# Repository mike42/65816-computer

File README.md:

# 65816 computer 

This is a prototype 65C816-based computer. It features a 1.8432 MHz processor, 1 megabyte of static RAM, a 65C22 I/O port, and an NXP SC16C752 dual UART.

The ROM contains a simple test program.

## Blog series

This is a learning project, and I am blogging about it as I progress.

- [A first look at the 65C816 processor](https://mike42.me/blog/2022-01-a-first-look-at-the-65c816-processor)
- [65C816 computer - initial prototype](https://mike42.me/blog/2022-02-65c816-computer-initial-prototype)
- [Interfacing an NXP UART to an 8-bit computer](https://mike42.me/blog/2022-02-interfacing-an-nxp-uart-to-an-8-bit-computer)
- [Let’s implement preemptive multitasking](https://mike42.me/blog/2022-03-lets-implement-preemptive-multitasking)
- [Building an emulator for my 65C816 computer](https://mike42.me/blog/2022-04-building-an-emulator-for-my-65c816-computer)
- [65C816 computer - second prototype](https://mike42.me/blog/2022-05-65c816-computer-second-prototype)
- [Building a 65C816 test board](https://mike42.me/blog/2022-06-building-a-65c816-test-board)
- [Let’s implement power-on self test (POST)](https://mike42.me/blog/2022-06-lets-implement-power-on-self-test-post)
- [Let’s make a bootloader – Part 1](https://mike42.me/blog/2022-09-lets-make-a-bootloader-part-1)
- [Let’s make a bootloader – Part 2](https://mike42.me/blog/2022-09-lets-make-a-bootloader-part-2)
- [Converting my 65C816 computer project to 3.3 V](https://mike42.me/blog/2023-01-converting-my-65c816-computer-project-to-3-3-v)

## Licenses & acknowledgement

With the exception of the files noted below, this work is © 2022-2023 Michael Billington, and is licensed under a [Creative Commons Attribution 4.0 International License](http://creativecommons.org/licenses/by/4.0/).

### 65816 emulator

The files in the `emulator/` directory are derived from Francesco Rigoni's work, primarily [lib65816](https://github.com/FrancescoRigoni/Lib65816). The emulator application is licensed under the GNU General Public License, version 3. Please see the README and LICENSE file in that directory for details.

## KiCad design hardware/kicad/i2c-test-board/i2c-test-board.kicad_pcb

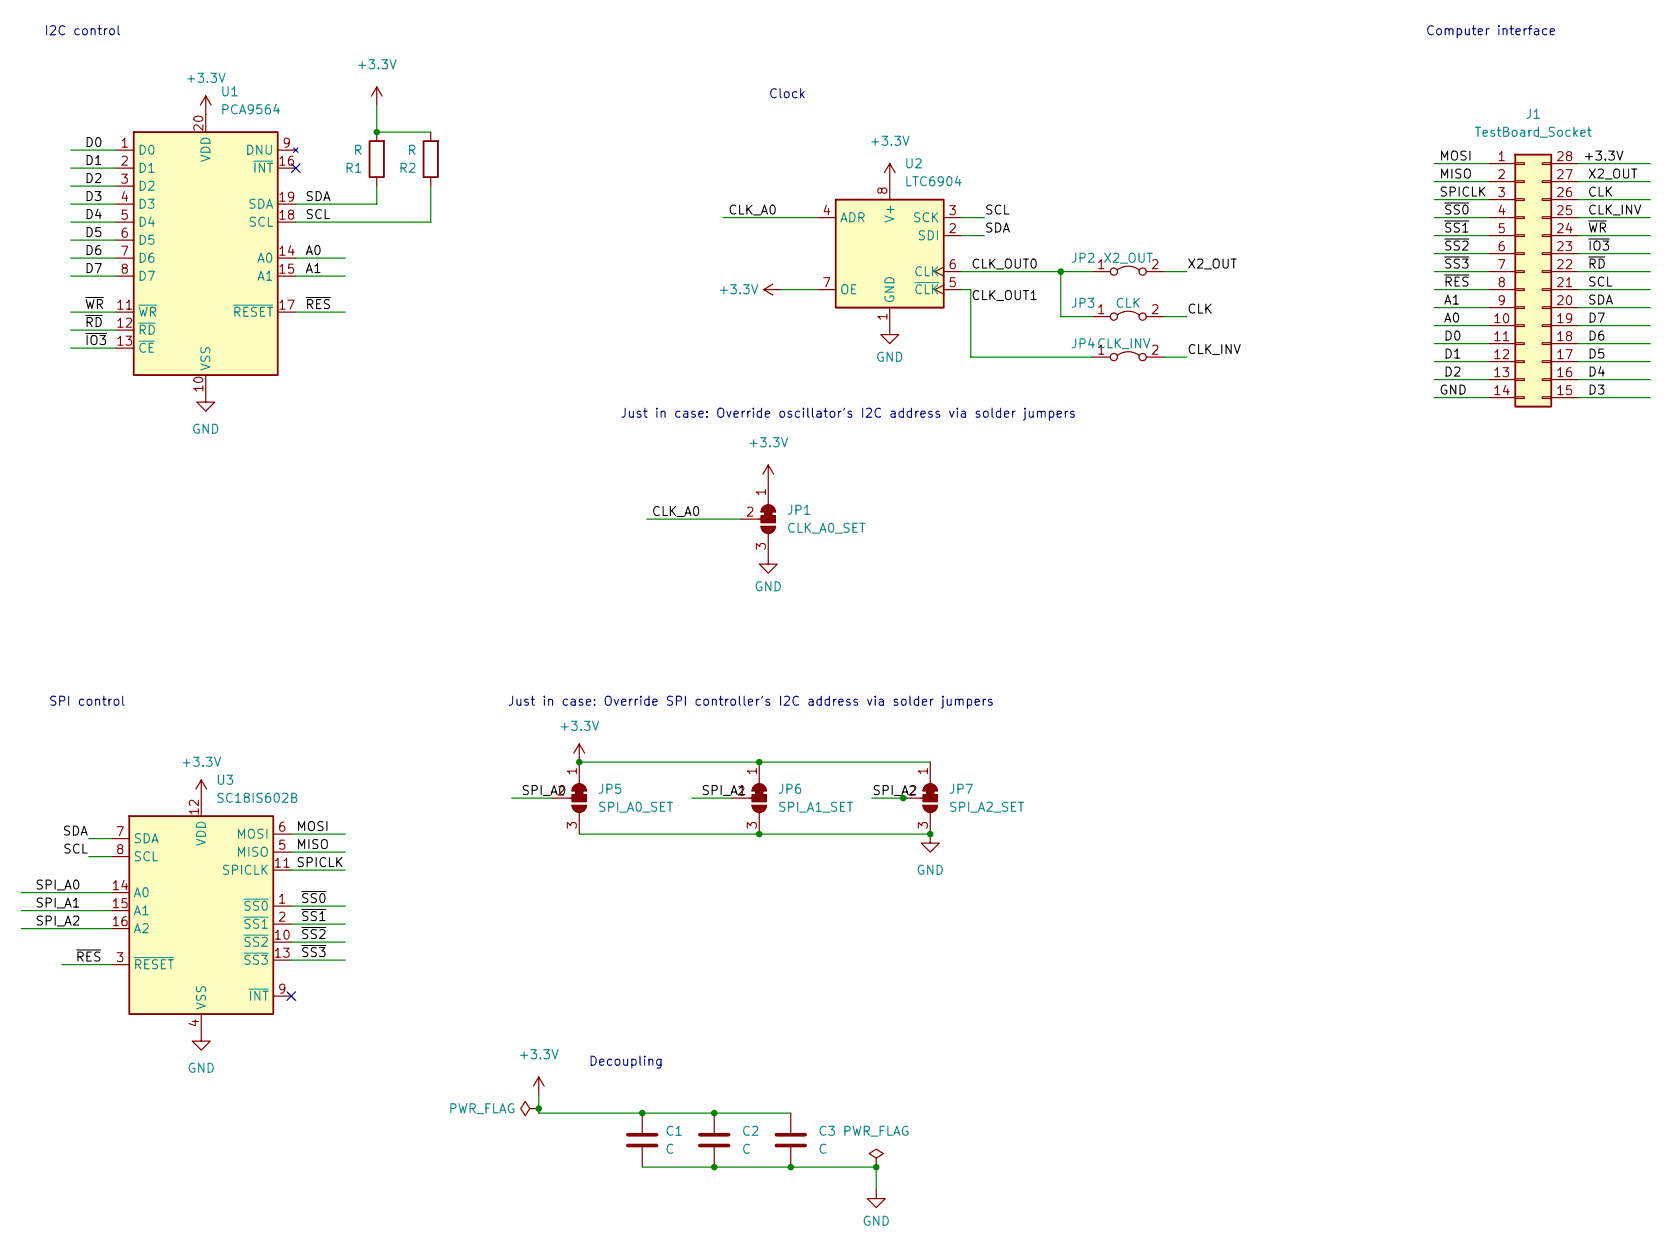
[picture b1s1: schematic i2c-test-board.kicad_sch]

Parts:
C1, C2, C3: C; C_0603_1608Metric_Pad1.08x0.95mm_HandSolder
J1: TestBoard_Socket; DIP-28_W15.24mm_Socket
JP1: CLK_A0_SET; SolderJumper-3_P1.3mm_Bridged12_RoundedPad1.0x1.5mm
JP2: X2_OUT; SolderJumper-2_P1.3mm_Bridged_RoundedPad1.0x1.5mm
JP3: CLK; SolderJumper-2_P1.3mm_Bridged_RoundedPad1.0x1.5mm
JP4: CLK_INV; SolderJumper-2_P1.3mm_Bridged_RoundedPad1.0x1.5mm
JP5: SPI_A0_SET; SolderJumper-3_P1.3mm_Bridged12_RoundedPad1.0x1.5mm
JP6: SPI_A1_SET; SolderJumper-3_P1.3mm_Bridged12_RoundedPad1.0x1.5mm
JP7: SPI_A2_SET; SolderJumper-3_P1.3mm_Bridged12_RoundedPad1.0x1.5mm
R1, R2: R; R_0603_1608Metric_Pad0.98x0.95mm_HandSolder
U1: PCA9564; TSSOP-20_4.4x6.5mm_P0.65mm
U2: LTC6904; MSOP-8_3x3mm_P0.65mm
U3: SC18IS602B; TSSOP-16_4.4x5mm_P0.65mm

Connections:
+3.3V: C1.1, C2.1, C3.1, J1.28, JP1.1 (A), JP5.1 (A), JP6.1 (A), JP7.1 (A), R1.2, R2.2, U1.20 (VDD), U2.7 (OE), U2.8 (V+), U3.12 (VDD)
/A0: J1.10, U1.14 (A0)
/A1: J1.9, U1.15 (A1)
/CLK: J1.26, JP3.2 (B)
/CLK_A0: JP1.2 (C), U2.4 (ADR)
/CLK_INV: J1.25, JP4.2 (B)
/CLK_OUT0: JP2.1 (A), JP3.1 (A), U2.6 (CLK)
/CLK_OUT1: JP4.1 (A), U2.5 (~CLK)
/D0: J1.11, U1.1 (D0)
/D1: J1.12, U1.2 (D1)
/D2: J1.13, U1.3 (D2)
/D3: J1.15, U1.4 (D3)
/D4: J1.16, U1.5 (D4)
/D5: J1.17, U1.6 (D5)
/D6: J1.18, U1.7 (D6)
/D7: J1.19, U1.8 (D7)
/MISO: J1.2, U3.5 (MISO)
/MOSI: J1.1, U3.6 (MOSI)
/SCL: J1.21, R2.1, U1.18 (SCL), U2.3 (SCK), U3.8 (SCL)
/SDA: J1.20, R1.1, U1.19 (SDA), U2.2 (SDI), U3.7 (SDA)
/SPICLK: J1.3, U3.11 (SPICLK)
/SPI_A0: JP5.2 (C), U3.14 (A0)
/SPI_A1: JP6.2 (C), U3.15 (A1)
/SPI_A2: JP7.2 (C), U3.16 (A2)
/X2_OUT: J1.27, JP2.2 (B)
/~IO3: J1.23, U1.13 (~CE)
/~RD: J1.22, U1.12 (~RD)
/~RES: J1.8, U1.17 (~RESET), U3.3 (~RESET)
/~SS0: J1.4, U3.1 (~SS0)
/~SS1: J1.5, U3.2 (~SS1)
/~SS2: J1.6, U3.10 (~SS2)
/~SS3: J1.7, U3.13 (~SS3)
/~WR: J1.24, U1.11 (~WR)
GND: C1.2, C2.2, C3.2, J1.14, JP1.3 (B), JP5.3 (B), JP6.3 (B), JP7.3 (B), U1.10 (VSS), U2.1 (GND), U3.4 (VSS)

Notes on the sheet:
I2C control
Just in case: Override oscillator's I2C address via solder jumpers
Computer interface
Clock
Decoupling
SPI control
Just in case: Override SPI controller's I2C address via solder jumpers

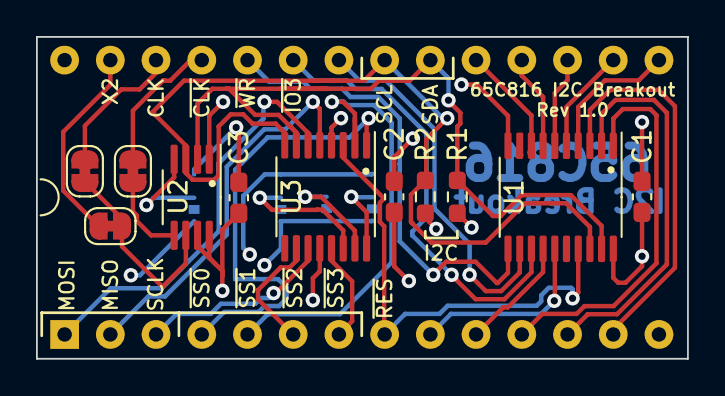
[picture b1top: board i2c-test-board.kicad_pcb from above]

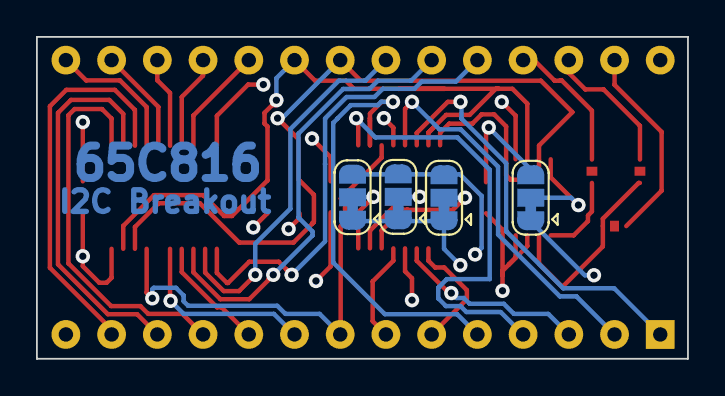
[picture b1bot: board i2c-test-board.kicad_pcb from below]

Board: 4 copper layers, 36.2 x 17.9 mm, 16 parts (4 on the bottom side), 34 nets.

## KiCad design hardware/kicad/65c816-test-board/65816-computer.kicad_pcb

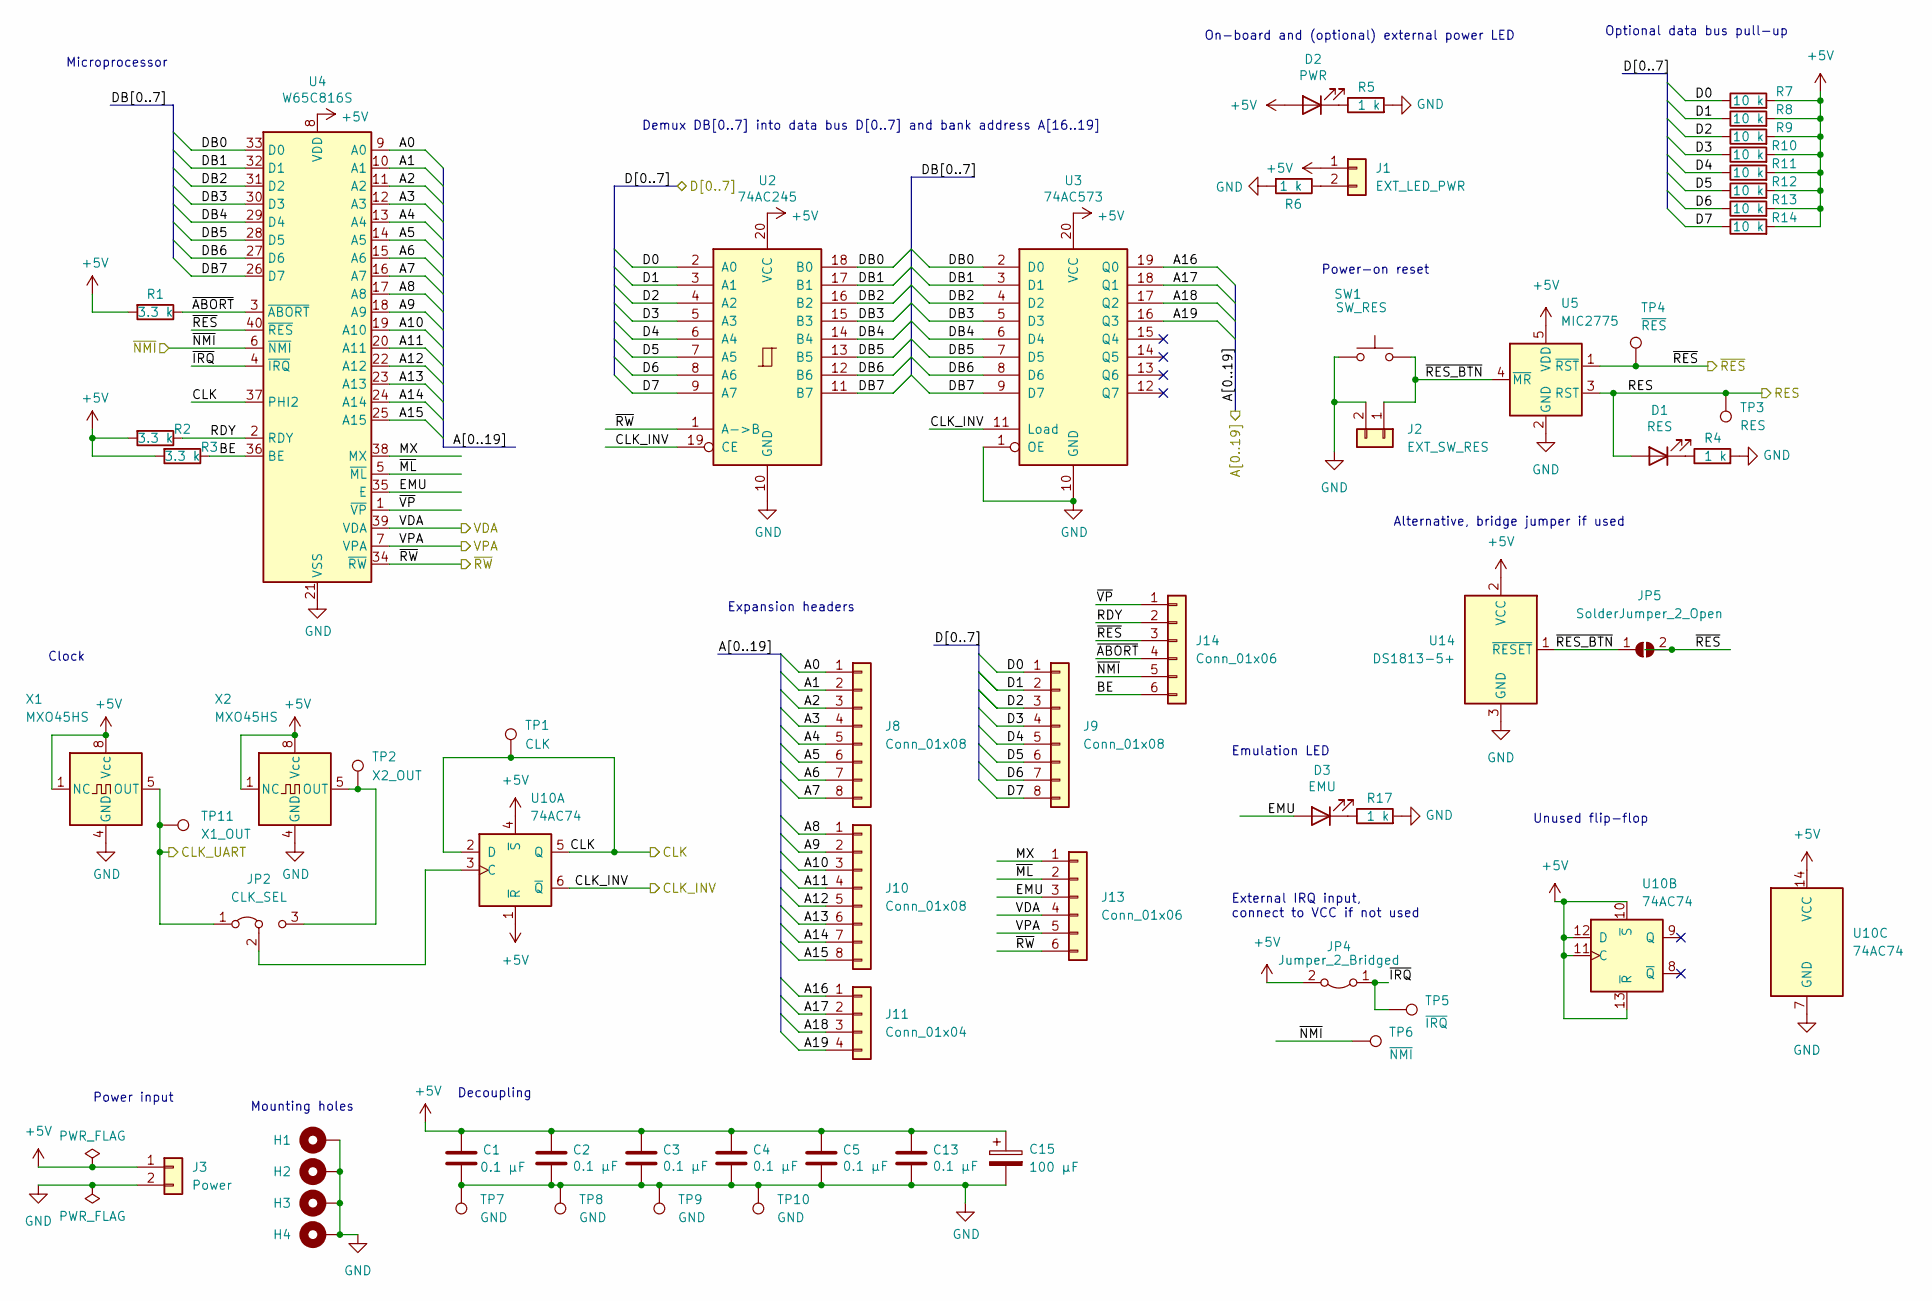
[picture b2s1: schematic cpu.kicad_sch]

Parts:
C1, C2, C3, C4, C5, C13: 0.1 µF; C_0603_1608Metric_Pad1.08x0.95mm_HandSolder
C15: 100 µF; CP_Radial_D6.3mm_P2.50mm
D1: RES; LED_0603_1608Metric_Pad1.05x0.95mm_HandSolder
D2: PWR; LED_0603_1608Metric_Pad1.05x0.95mm_HandSolder
D3: EMU; LED_0603_1608Metric_Pad1.05x0.95mm_HandSolder
H1, H2, H3, H4: MountingHole_Pad; MountingHole_3.2mm_M3_Pad_Via
J1: EXT_LED_PWR; PinHeader_1x02_P2.54mm_Vertical
J2: EXT_SW_RES; PinHeader_1x02_P2.54mm_Vertical
J3: Power; JST_XH_B2B-XH-A_1x02_P2.50mm_Vertical
J8, J9, J10: Conn_01x08; PinHeader_1x08_P2.54mm_Vertical
J11: Conn_01x04; PinHeader_1x04_P2.54mm_Vertical
J13, J14: Conn_01x06; PinHeader_1x06_P2.54mm_Vertical
JP2: CLK_SEL; PinHeader_1x03_P2.54mm_Vertical
JP4: Jumper_2_Bridged; PinHeader_1x02_P2.54mm_Vertical
JP5: SolderJumper_2_Open; SolderJumper-2_P1.3mm_Open_RoundedPad1.0x1.5mm
R1, R2, R3: 3.3 k; R_0603_1608Metric_Pad0.98x0.95mm_HandSolder
R4, R5, R6, R17: 1 k; R_0603_1608Metric_Pad0.98x0.95mm_HandSolder
R7, R8, R9, R10, R11, R12, R13, R14: 10 k; R_0603_1608Metric_Pad0.98x0.95mm_HandSolder
SW1: SW_RES; SW_TH_Tactile_Omron_B3F-10xx
TP1: CLK; TestPoint_Keystone_5005-5009_Compact
TP2: X2_OUT; TestPoint_Keystone_5005-5009_Compact
TP3: RES; TestPoint_Pad_D1.5mm
TP4: ~{RES}; TestPoint_Keystone_5005-5009_Compact
TP5: ~{IRQ}; TestPoint_Keystone_5005-5009_Compact
TP6: ~{NMI}; TestPoint_Keystone_5005-5009_Compact
TP7, TP8, TP9, TP10: GND; TestPoint_Keystone_5005-5009_Compact
TP11: X1_OUT; TestPoint_Keystone_5005-5009_Compact
U2: 74AC245; DIP-20_W7.62mm_Socket
U3: 74AC573; DIP-20_W7.62mm_Socket
U4: W65C816S; DIP-40_W15.24mm_Socket
U5: MIC2775; SOT-23-5_HandSoldering
U10: 74AC74; DIP-14_W7.62mm_Socket
U14: DS1813-5+; TO-92_Inline
X1, X2: MXO45HS; Oscillator_DIP-8

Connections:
+5V: C1.1, C2.1, C3.1, C4.1, C5.1, C13.1, C15.1, D2.2 (A), J1.1, J3.1, JP4.2 (B), R1.2, R2.2, R3.2, R7.2, R8.2, R9.2, R10.2, R11.2, R12.2, R13.2, R14.2, U2.20 (VCC), U3.20 (VCC), U4.8 (VDD), U5.5 (VDD), U10.1 (~R), U10.4 (~S), U10.10 (~S), U10.11 (C), U10.12 (D), U10.13 (~R), U10.14 (VCC), U14.2 (VCC), X1.1 (NC), X1.8 (Vcc), X2.1 (NC), X2.8 (Vcc); also elsewhere on the board
/CPU& Bank Address Latching/A0: J8.1, U4.9 (A0); also elsewhere on the board
/CPU& Bank Address Latching/A1: J8.2, U4.10 (A1); also elsewhere on the board
/CPU& Bank Address Latching/A2: J8.3, U4.11 (A2); also elsewhere on the board
/CPU& Bank Address Latching/A3: J8.4, U4.12 (A3); also elsewhere on the board
/CPU& Bank Address Latching/A4: J8.5, U4.13 (A4); also elsewhere on the board
/CPU& Bank Address Latching/A5: J8.6, U4.14 (A5); also elsewhere on the board
/CPU& Bank Address Latching/A6: J8.7, U4.15 (A6); also elsewhere on the board
/CPU& Bank Address Latching/A7: J8.8, U4.16 (A7); also elsewhere on the board
/CPU& Bank Address Latching/A8: J10.1, U4.17 (A8); also elsewhere on the board
/CPU& Bank Address Latching/A9: J10.2, U4.18 (A9); also elsewhere on the board
/CPU& Bank Address Latching/A10: J10.3, U4.19 (A10); also elsewhere on the board
/CPU& Bank Address Latching/A11: J10.4, U4.20 (A11); also elsewhere on the board
/CPU& Bank Address Latching/A12: J10.5, U4.22 (A12); also elsewhere on the board
/CPU& Bank Address Latching/A13: J10.6, U4.23 (A13); also elsewhere on the board
/CPU& Bank Address Latching/A14: J10.7, U4.24 (A14); also elsewhere on the board
/CPU& Bank Address Latching/A15: J10.8, U4.25 (A15); also elsewhere on the board
/CPU& Bank Address Latching/A16: J11.1, U3.19 (Q0); also elsewhere on the board
/CPU& Bank Address Latching/A17: J11.2, U3.18 (Q1); also elsewhere on the board
/CPU& Bank Address Latching/A18: J11.3, U3.17 (Q2); also elsewhere on the board
/CPU& Bank Address Latching/A19: J11.4, U3.16 (Q3); also elsewhere on the board
/CPU& Bank Address Latching/BE: J14.6, R3.1, U4.36 (BE)
/CPU& Bank Address Latching/CLK: TP1.1, U4.37 (PHI2), U10.2 (D), U10.5 (Q); also elsewhere on the board
/CPU& Bank Address Latching/CLK_INV: U2.19 (CE), U3.11 (Load), U10.6 (~Q)
/CPU& Bank Address Latching/CLK_UART: JP2.1 (A), TP11.1, X1.5 (OUT); also elsewhere on the board
/CPU& Bank Address Latching/D0: J9.1, R7.1, U2.2 (A0); also elsewhere on the board
/CPU& Bank Address Latching/D1: J9.2, R8.1, U2.3 (A1); also elsewhere on the board
/CPU& Bank Address Latching/D2: J9.3, R9.1, U2.4 (A2); also elsewhere on the board
/CPU& Bank Address Latching/D3: J9.4, R10.1, U2.5 (A3); also elsewhere on the board
/CPU& Bank Address Latching/D4: J9.5, R11.1, U2.6 (A4); also elsewhere on the board
/CPU& Bank Address Latching/D5: J9.6, R12.1, U2.7 (A5); also elsewhere on the board
/CPU& Bank Address Latching/D6: J9.7, R13.1, U2.8 (A6); also elsewhere on the board
/CPU& Bank Address Latching/D7: J9.8, R14.1, U2.9 (A7); also elsewhere on the board
/CPU& Bank Address Latching/DB0: U2.18 (B0), U3.2 (D0), U4.33 (D0)
/CPU& Bank Address Latching/DB1: U2.17 (B1), U3.3 (D1), U4.32 (D1)
/CPU& Bank Address Latching/DB2: U2.16 (B2), U3.4 (D2), U4.31 (D2)
/CPU& Bank Address Latching/DB3: U2.15 (B3), U3.5 (D3), U4.30 (D3)
/CPU& Bank Address Latching/DB4: U2.14 (B4), U3.6 (D4), U4.29 (D4)
/CPU& Bank Address Latching/DB5: U2.13 (B5), U3.7 (D5), U4.28 (D5)
/CPU& Bank Address Latching/DB6: U2.12 (B6), U3.8 (D6), U4.27 (D6)
/CPU& Bank Address Latching/DB7: U2.11 (B7), U3.9 (D7), U4.26 (D7)
/CPU& Bank Address Latching/EMU: D3.2 (A), J13.3, U4.35 (E)
/CPU& Bank Address Latching/MX: J13.1, U4.38 (MX)
/CPU& Bank Address Latching/RDY: J14.2, R2.1, U4.2 (RDY)
/CPU& Bank Address Latching/RES: D1.2 (A), TP3.1, U5.3 (RST); also elsewhere on the board
/CPU& Bank Address Latching/VDA: J13.4, U4.39 (VDA); also elsewhere on the board
/CPU& Bank Address Latching/VPA: J13.5, U4.7 (VPA); also elsewhere on the board
/CPU& Bank Address Latching/~ABORT: J14.4, R1.1, U4.3 (~ABORT)
/CPU& Bank Address Latching/~IRQ: JP4.1 (A), TP5.1, U4.4 (~IRQ)
/CPU& Bank Address Latching/~ML: J13.2, U4.5 (~ML)
/CPU& Bank Address Latching/~NMI: J14.5, TP6.1, U4.6 (~NMI); also elsewhere on the board
/CPU& Bank Address Latching/~RES_BTN: J2.1, JP5.1 (A), SW1.2, U5.4 (~MR), U14.1 (~RESET)
/CPU& Bank Address Latching/~RES: J14.3, JP5.2 (B), TP4.1, U4.40 (~RES), U5.1 (~RST); also elsewhere on the board
/CPU& Bank Address Latching/~RW: J13.6, U2.1 (A->B), U4.34 (~RW); also elsewhere on the board
/CPU& Bank Address Latching/~VP: J14.1, U4.1 (~VP)
GND: C1.2, C2.2, C3.2, C4.2, C5.2, C13.2, C15.2, H1.1, H2.1, H3.1, H4.1, J2.2, J3.2, R4.2, R5.2, R6.2, R17.2, SW1.1, TP7.1, TP8.1, TP9.1, TP10.1, U2.10 (GND), U3.1 (OE), U3.10 (GND), U4.21 (VSS), U5.2 (GND), U10.7 (GND), U14.3 (GND), X1.4 (GND), X2.4 (GND); also elsewhere on the board
unnamed: D1.1 (K), R4.1
unnamed: D2.1 (K), R5.1
unnamed: D3.1 (K), R17.1
unnamed: J1.2, R6.1
unnamed: JP2.2 (C), U10.3 (C)
unnamed 127: JP2.3 (B), TP2.1, X2.5 (OUT); also elsewhere on the board

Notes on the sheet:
Power input
Unused flip-flop
Expansion headers
On-board and (optional) external power LED
Microprocessor
Clock
Alternative, bridge jumper if used
Emulation LED
Demux DB[0..7] into data bus D[0..7] and bank address A[16..19]
Decoupling
Mounting holes
External IRQ input, connect to VCC if not used
Power-on reset
Optional data bus pull-up

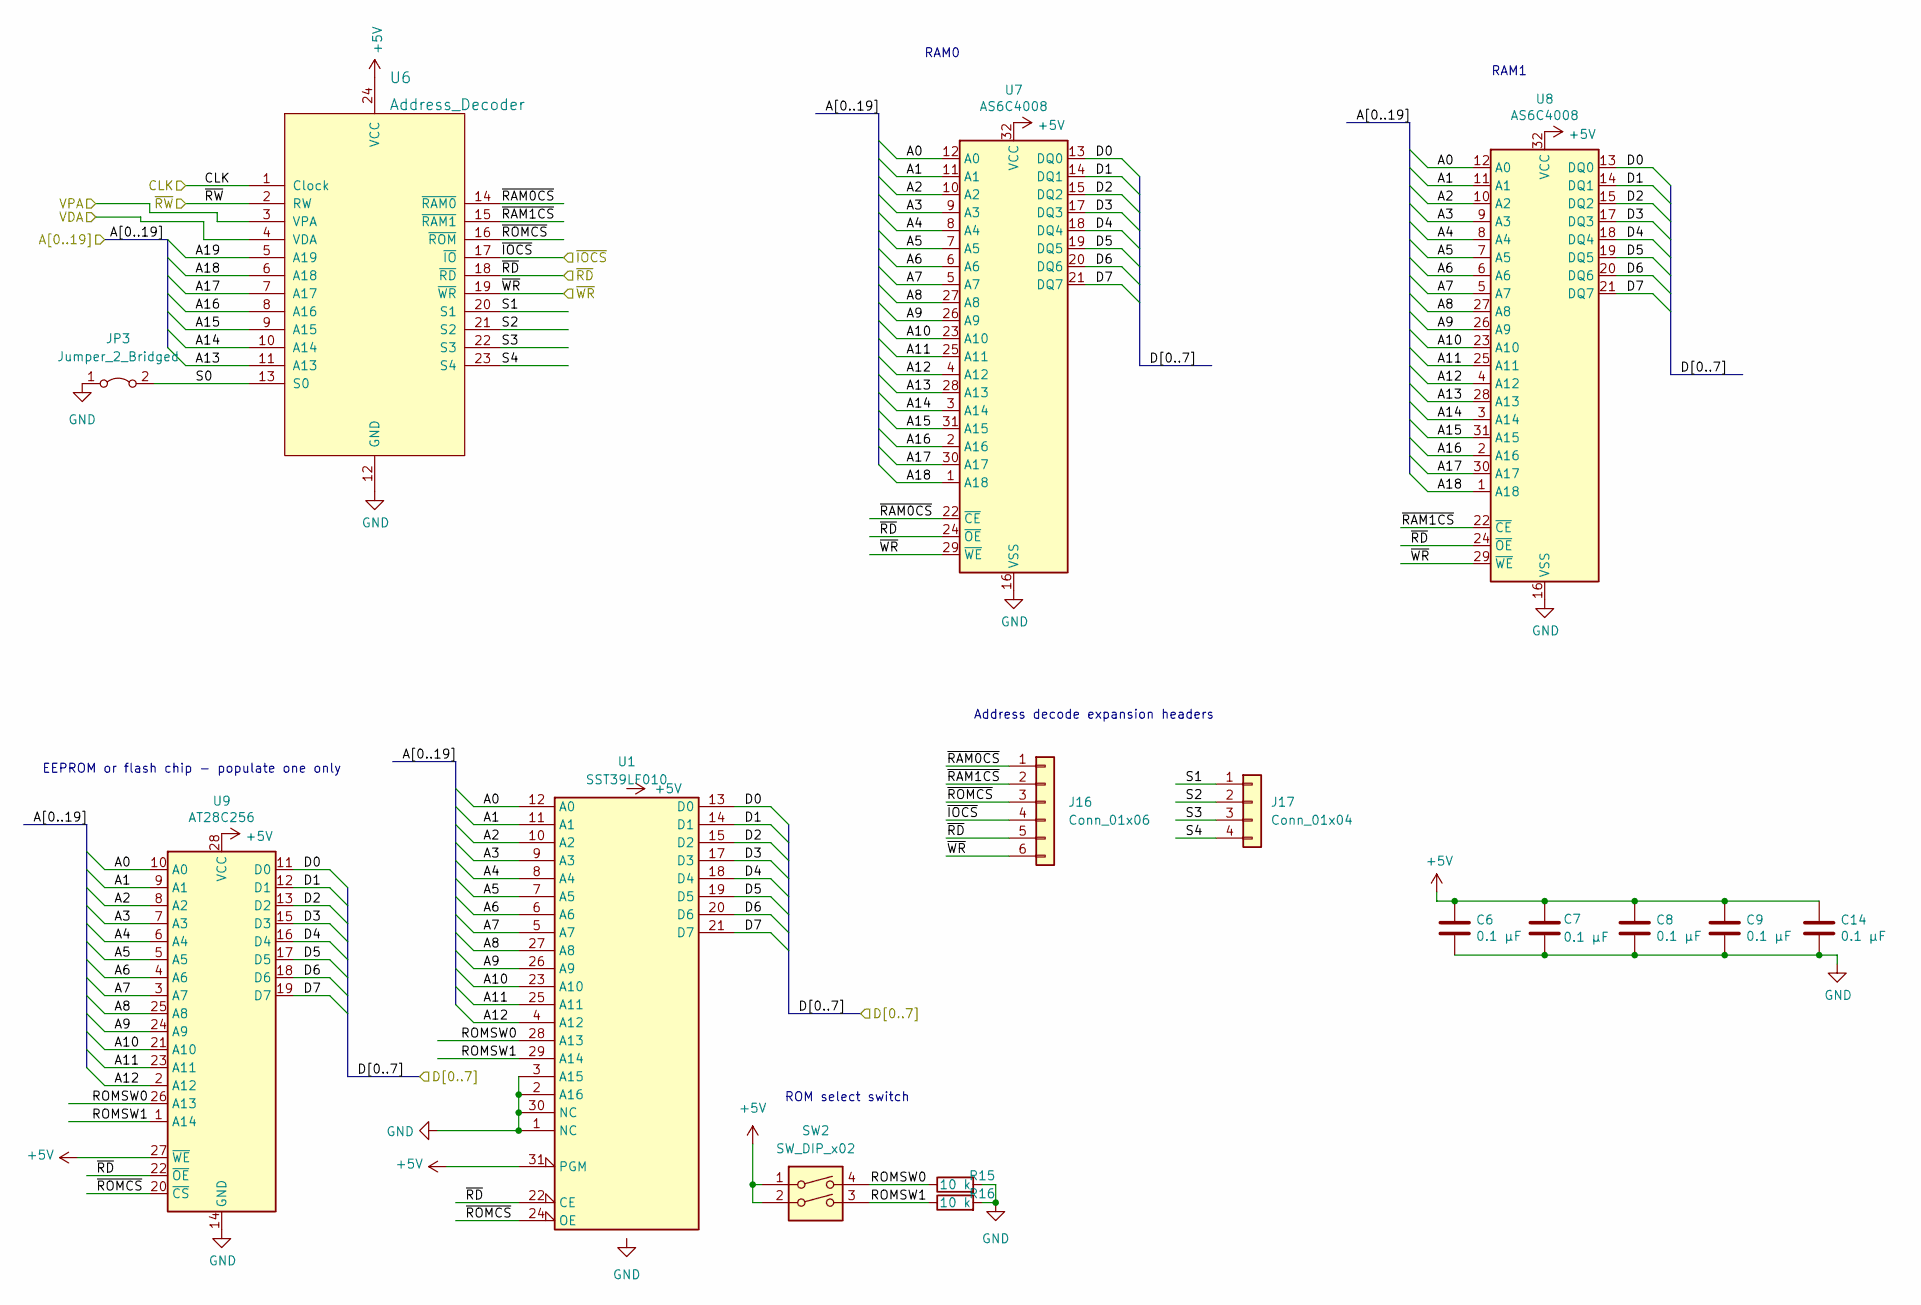
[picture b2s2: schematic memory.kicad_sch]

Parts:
C6, C7, C8, C9, C14: 0.1 µF; C_0603_1608Metric_Pad1.08x0.95mm_HandSolder
J16: Conn_01x06; PinHeader_1x06_P2.54mm_Vertical
J17: Conn_01x04; PinHeader_1x04_P2.54mm_Vertical
JP3: Jumper_2_Bridged; PinHeader_1x02_P2.54mm_Vertical
R15, R16: 10 k; R_0603_1608Metric_Pad0.98x0.95mm_HandSolder
SW2: SW_DIP_x02; SW_DIP_SPSTx02_Slide_6.7x6.64mm_W8.61mm_P2.54mm_LowProfile
U1: SST39LF010; PLCC-32_11.4x14.0mm_P1.27mm
U6: Address_Decoder; DIP-24_W7.62mm_Socket
U7, U8: AS6C4008; DIP-32_W15.24mm_Socket
U9: AT28C256; DIP-28_W15.24mm_Socket

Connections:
+5V: C6.1, C7.1, C8.1, C9.1, C14.1, SW2.1, SW2.2, U1.31 (PGM), U1.32 (VCC), U6.24 (VCC), U7.32 (VCC), U8.32 (VCC), U9.27 (~WE), U9.28 (VCC); also elsewhere on the board
/CPU& Bank Address Latching/A0: U1.12 (A0), U7.12 (A0), U8.12 (A0), U9.10 (A0); also elsewhere on the board
/CPU& Bank Address Latching/A1: U1.11 (A1), U7.11 (A1), U8.11 (A1), U9.9 (A1); also elsewhere on the board
/CPU& Bank Address Latching/A2: U1.10 (A2), U7.10 (A2), U8.10 (A2), U9.8 (A2); also elsewhere on the board
/CPU& Bank Address Latching/A3: U1.9 (A3), U7.9 (A3), U8.9 (A3), U9.7 (A3); also elsewhere on the board
/CPU& Bank Address Latching/A4: U1.8 (A4), U7.8 (A4), U8.8 (A4), U9.6 (A4); also elsewhere on the board
/CPU& Bank Address Latching/A5: U1.7 (A5), U7.7 (A5), U8.7 (A5), U9.5 (A5); also elsewhere on the board
/CPU& Bank Address Latching/A6: U1.6 (A6), U7.6 (A6), U8.6 (A6), U9.4 (A6); also elsewhere on the board
/CPU& Bank Address Latching/A7: U1.5 (A7), U7.5 (A7), U8.5 (A7), U9.3 (A7); also elsewhere on the board
/CPU& Bank Address Latching/A8: U1.27 (A8), U7.27 (A8), U8.27 (A8), U9.25 (A8); also elsewhere on the board
/CPU& Bank Address Latching/A9: U1.26 (A9), U7.26 (A9), U8.26 (A9), U9.24 (A9); also elsewhere on the board
/CPU& Bank Address Latching/A10: U1.23 (A10), U7.23 (A10), U8.23 (A10), U9.21 (A10); also elsewhere on the board
/CPU& Bank Address Latching/A11: U1.25 (A11), U7.25 (A11), U8.25 (A11), U9.23 (A11); also elsewhere on the board
/CPU& Bank Address Latching/A12: U1.4 (A12), U7.4 (A12), U8.4 (A12), U9.2 (A12); also elsewhere on the board
/CPU& Bank Address Latching/A13: U6.11 (A13), U7.28 (A13), U8.28 (A13); also elsewhere on the board
/CPU& Bank Address Latching/A14: U6.10 (A14), U7.3 (A14), U8.3 (A14); also elsewhere on the board
/CPU& Bank Address Latching/A15: U6.9 (A15), U7.31 (A15), U8.31 (A15); also elsewhere on the board
/CPU& Bank Address Latching/A16: U6.8 (A16), U7.2 (A16), U8.2 (A16); also elsewhere on the board
/CPU& Bank Address Latching/A17: U6.7 (A17), U7.30 (A17), U8.30 (A17); also elsewhere on the board
/CPU& Bank Address Latching/A18: U6.6 (A18), U7.1 (A18), U8.1 (A18); also elsewhere on the board
/CPU& Bank Address Latching/A19: U6.5 (A19); also elsewhere on the board
/CPU& Bank Address Latching/CLK: U6.1 (Clock); also elsewhere on the board
/CPU& Bank Address Latching/D0: U1.13 (D0), U7.13 (DQ0), U8.13 (DQ0), U9.11 (D0); also elsewhere on the board
/CPU& Bank Address Latching/D1: U1.14 (D1), U7.14 (DQ1), U8.14 (DQ1), U9.12 (D1); also elsewhere on the board
/CPU& Bank Address Latching/D2: U1.15 (D2), U7.15 (DQ2), U8.15 (DQ2), U9.13 (D2); also elsewhere on the board
/CPU& Bank Address Latching/D3: U1.17 (D3), U7.17 (DQ3), U8.17 (DQ3), U9.15 (D3); also elsewhere on the board
/CPU& Bank Address Latching/D4: U1.18 (D4), U7.18 (DQ4), U8.18 (DQ4), U9.16 (D4); also elsewhere on the board
/CPU& Bank Address Latching/D5: U1.19 (D5), U7.19 (DQ5), U8.19 (DQ5), U9.17 (D5); also elsewhere on the board
/CPU& Bank Address Latching/D6: U1.20 (D6), U7.20 (DQ6), U8.20 (DQ6), U9.18 (D6); also elsewhere on the board
/CPU& Bank Address Latching/D7: U1.21 (D7), U7.21 (DQ7), U8.21 (DQ7), U9.19 (D7); also elsewhere on the board
/CPU& Bank Address Latching/VDA: U6.4 (VDA); also elsewhere on the board
/CPU& Bank Address Latching/VPA: U6.3 (VPA); also elsewhere on the board
/CPU& Bank Address Latching/~RW: U6.2 (RW); also elsewhere on the board
/IO/~IOCS: J16.4, U6.17 (~IO); also elsewhere on the board
/Memory/ROMSW0: R15.1, SW2.4, U1.28 (A13), U9.26 (A13)
/Memory/ROMSW1: R16.1, SW2.3, U1.29 (A14), U9.1 (A14)
/Memory/S0: JP3.2 (B), U6.13 (S0)
/Memory/S1: J17.1, U6.20 (S1)
/Memory/S2: J17.2, U6.21 (S2)
/Memory/S3: J17.3, U6.22 (S3)
/Memory/S4: J17.4, U6.23 (S4)
/Memory/~RAM0CS: J16.1, U6.14 (~RAM0), U7.22 (~CE)
/Memory/~RAM1CS: J16.2, U6.15 (~RAM1), U8.22 (~CE)
/Memory/~RD: J16.5, U1.22 (CE), U6.18 (~RD), U7.24 (~OE), U8.24 (~OE), U9.22 (~OE); also elsewhere on the board
/Memory/~ROMCS: J16.3, U1.24 (OE), U6.16 (~ROM), U9.20 (~CS)
/Memory/~WR: J16.6, U6.19 (~WR), U7.29 (~WE), U8.29 (~WE); also elsewhere on the board
GND: C6.2, C7.2, C8.2, C9.2, C14.2, JP3.1 (A), R15.2, R16.2, U1.1 (NC), U1.2 (A16), U1.3 (A15), U1.16 (GND), U1.30 (NC), U6.12 (GND), U7.16 (VSS), U8.16 (VSS), U9.14 (GND); also elsewhere on the board

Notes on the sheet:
EEPROM or flash chip - populate one only
ROM select switch
Address decode expansion headers
RAM0
RAM1

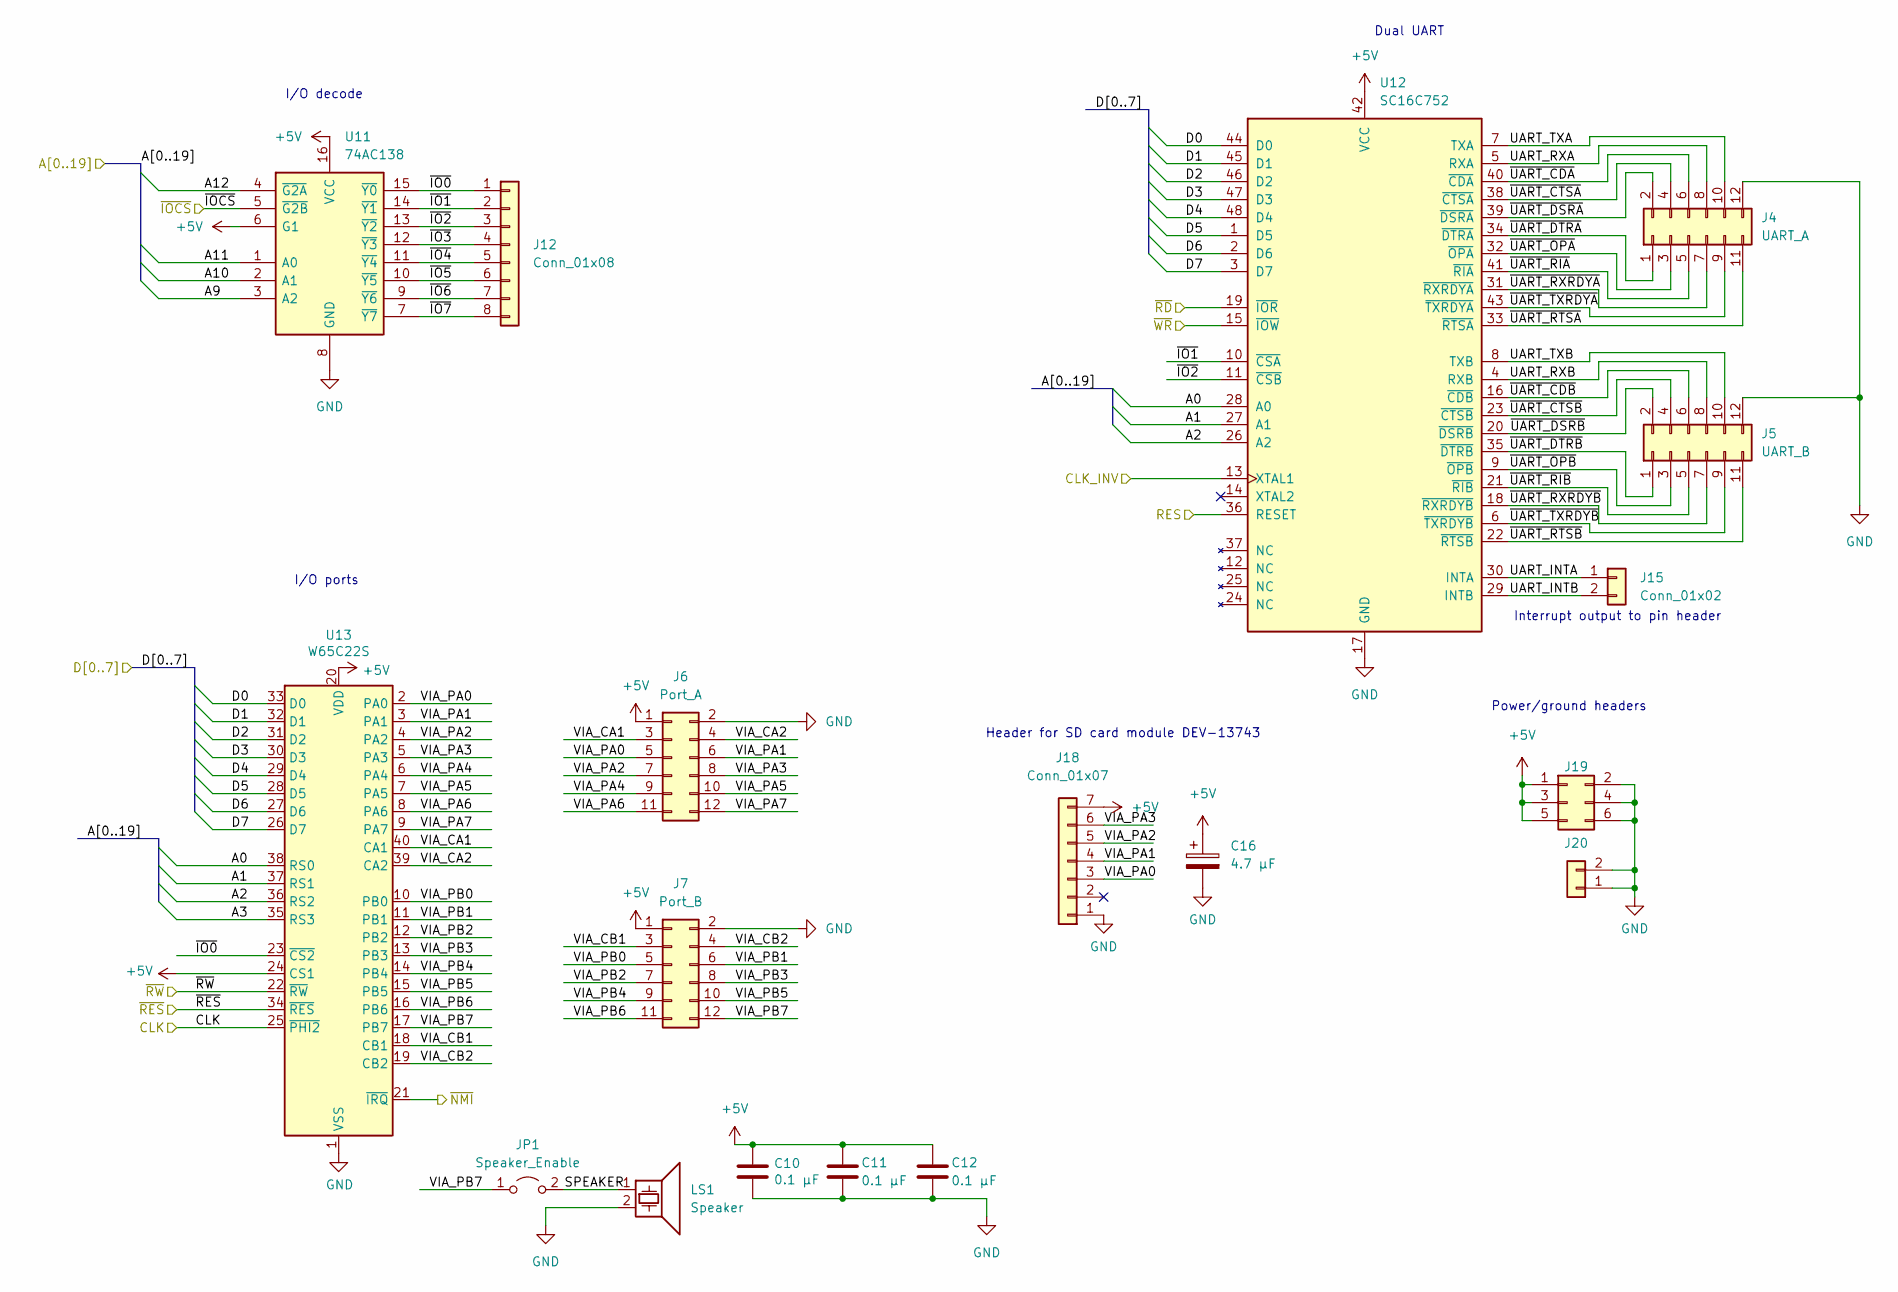
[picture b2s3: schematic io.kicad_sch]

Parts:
C10, C11, C12: 0.1 µF; C_0603_1608Metric_Pad1.08x0.95mm_HandSolder
C16: 4.7 µF; CP_Radial_D4.0mm_P1.50mm
J4: UART_A; PinHeader_2x06_P2.54mm_Vertical
J5: UART_B; PinHeader_2x06_P2.54mm_Vertical
J6: Port_A; PinHeader_2x06_P2.54mm_Vertical
J7: Port_B; PinHeader_2x06_P2.54mm_Vertical
J12: Conn_01x08; PinHeader_1x08_P2.54mm_Vertical
J15: Conn_01x02; PinHeader_1x02_P2.54mm_Vertical
J18: Conn_01x07; PinSocket_1x07_P2.54mm_Vertical
J19, J20: (no value)
JP1: Speaker_Enable; PinHeader_1x02_P2.54mm_Vertical
LS1: Speaker; Buzzer_TDK_PS1240P02BT_D12.2mm_H6.5mm
U11: 74AC138; DIP-16_W7.62mm_Socket
U12: SC16C752; LQFP-48_7x7mm_P0.5mm
U13: W65C22S; DIP-40_W15.24mm_Socket

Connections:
+5V: C10.1, C11.1, C12.1, C16.1, J6.1, J7.1, J18.7, J19.1, J19.3, J19.5, U11.6 (G1), U11.16 (VCC), U12.42 (VCC), U13.20 (VDD), U13.24 (CS1); also elsewhere on the board
/CPU& Bank Address Latching/A0: U12.28 (A0), U13.38 (RS0); also elsewhere on the board
/CPU& Bank Address Latching/A1: U12.27 (A1), U13.37 (RS1); also elsewhere on the board
/CPU& Bank Address Latching/A2: U12.26 (A2), U13.36 (RS2); also elsewhere on the board
/CPU& Bank Address Latching/A3: U13.35 (RS3); also elsewhere on the board
/CPU& Bank Address Latching/A9: U11.3 (A2); also elsewhere on the board
/CPU& Bank Address Latching/A10: U11.2 (A1); also elsewhere on the board
/CPU& Bank Address Latching/A11: U11.1 (A0); also elsewhere on the board
/CPU& Bank Address Latching/A12: U11.4 (~G2A); also elsewhere on the board
/CPU& Bank Address Latching/CLK: U13.25 (~PHI2); also elsewhere on the board
/CPU& Bank Address Latching/CLK_UART: U12.13 (XTAL1); also elsewhere on the board
/CPU& Bank Address Latching/D0: U12.44 (D0), U13.33 (D0); also elsewhere on the board
/CPU& Bank Address Latching/D1: U12.45 (D1), U13.32 (D1); also elsewhere on the board
/CPU& Bank Address Latching/D2: U12.46 (D2), U13.31 (D2); also elsewhere on the board
/CPU& Bank Address Latching/D3: U12.47 (D3), U13.30 (D3); also elsewhere on the board
/CPU& Bank Address Latching/D4: U12.48 (D4), U13.29 (D4); also elsewhere on the board
/CPU& Bank Address Latching/D5: U12.1 (D5), U13.28 (D5); also elsewhere on the board
/CPU& Bank Address Latching/D6: U12.2 (D6), U13.27 (D6); also elsewhere on the board
/CPU& Bank Address Latching/D7: U12.3 (D7), U13.26 (D7); also elsewhere on the board
/CPU& Bank Address Latching/RES: J15.3, U12.36 (RESET); also elsewhere on the board
/CPU& Bank Address Latching/~NMI: U13.21 (~IRQ); also elsewhere on the board
/CPU& Bank Address Latching/~RES: U13.34 (~RES); also elsewhere on the board
/CPU& Bank Address Latching/~RW: U13.22 (~RW); also elsewhere on the board
/IO/SPEAKER: JP1.2 (B), LS1.1
/IO/UART_INTA: J15.1, U12.30 (INTA)
/IO/UART_INTB: J15.2, U12.29 (INTB)
/IO/UART_RXA: J4.8, U12.5 (RXA)
/IO/UART_RXB: J5.8, U12.4 (RXB)
/IO/UART_TXA: J4.10, U12.7 (TXA)
/IO/UART_TXB: J5.10, U12.8 (TXB)
/IO/VIA_CA1: J6.3, U13.40 (CA1)
/IO/VIA_CA2: J6.4, U13.39 (CA2)
/IO/VIA_CB1: J7.3, U13.18 (CB1)
/IO/VIA_CB2: J7.4, U13.19 (CB2)
/IO/VIA_PA0: J6.5, J18.3, U13.2 (PA0)
/IO/VIA_PA1: J6.6, J18.4, U13.3 (PA1)
/IO/VIA_PA2: J6.7, J18.5, U13.4 (PA2)
/IO/VIA_PA3: J6.8, J18.6, U13.5 (PA3)
/IO/VIA_PA4: J6.9, U13.6 (PA4)
/IO/VIA_PA5: J6.10, U13.7 (PA5)
/IO/VIA_PA6: J6.11, U13.8 (PA6)
/IO/VIA_PA7: J6.12, U13.9 (PA7)
/IO/VIA_PB0: J7.5, U13.10 (PB0)
/IO/VIA_PB1: J7.6, U13.11 (PB1)
/IO/VIA_PB2: J7.7, U13.12 (PB2)
/IO/VIA_PB3: J7.8, U13.13 (PB3)
/IO/VIA_PB4: J7.9, U13.14 (PB4)
/IO/VIA_PB5: J7.10, U13.15 (PB5)
/IO/VIA_PB6: J7.11, U13.16 (PB6)
/IO/VIA_PB7: J7.12, JP1.1 (A), U13.17 (PB7)
/IO/~IO0: J12.1, U11.15 (~Y0), U13.23 (~CS2)
/IO/~IO1: J12.2, U11.14 (~Y1), U12.10 (~CSA)
/IO/~IO2: J12.3, U11.13 (~Y2), U12.11 (~CSB)
/IO/~IO3: J12.4, U11.12 (~Y3)
/IO/~IO4: J12.5, U11.11 (~Y4)
/IO/~IO5: J12.6, U11.10 (~Y5)
/IO/~IO6: J12.7, U11.9 (~Y6)
/IO/~IO7: J12.8, U11.7 (~Y7)
/IO/~IOCS: U11.5 (~G2B); also elsewhere on the board
/IO/~UART_CDA: J4.6, U12.40 (~CDA)
/IO/~UART_CDB: J5.6, U12.16 (~CDB)
/IO/~UART_CTSA: J4.4, U12.38 (~CTSA)
/IO/~UART_CTSB: J5.4, U12.23 (~CTSB)
/IO/~UART_DSRA: J4.2, U12.39 (~DSRA)
/IO/~UART_DSRB: J5.2, U12.20 (~DSRB)
/IO/~UART_DTRA: J4.1, U12.34 (~DTRA)
/IO/~UART_DTRB: J5.1, U12.35 (~DTRB)
/IO/~UART_OPA: J4.3, U12.32 (~OPA)
/IO/~UART_OPB: J5.3, U12.9 (~OPB)
/IO/~UART_RIA: J4.5, U12.41 (~RIA)
/IO/~UART_RIB: J5.5, U12.21 (~RIB)
/IO/~UART_RTSA: J4.11, U12.33 (~RTSA)
/IO/~UART_RTSB: J5.11, U12.22 (~RTSB)
/IO/~UART_RXRDYA: J4.7, U12.31 (~RXRDYA)
/IO/~UART_RXRDYB: J5.7, U12.18 (~RXRDYB)
/IO/~UART_TXRDYA: J4.9, U12.43 (~TXRDYA)
/IO/~UART_TXRDYB: J5.9, U12.6 (~TXRDYB)
/Memory/~RD: U12.19 (~IOR); also elsewhere on the board
/Memory/~WR: U12.15 (~IOW); also elsewhere on the board
GND: C10.2, C11.2, C12.2, C16.2, J4.12, J5.12, J6.2, J7.2, J18.1, J19.2, J19.4, J19.6, J20.1, J20.2, LS1.2, U11.8 (GND), U12.17 (GND), U13.1 (VSS); also elsewhere on the board

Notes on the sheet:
Header for SD card module DEV-13743
I/O decode
Dual UART
Power/ground headers
Interrupt output to pin header
I/O ports

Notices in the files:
hardware/kicad/65c816-test-board/65816-computer.kicad_pcb:
© 2022 Michael Billington
